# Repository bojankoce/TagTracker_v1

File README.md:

# TagTracker_v1
Version 1 of the Tag Tracker

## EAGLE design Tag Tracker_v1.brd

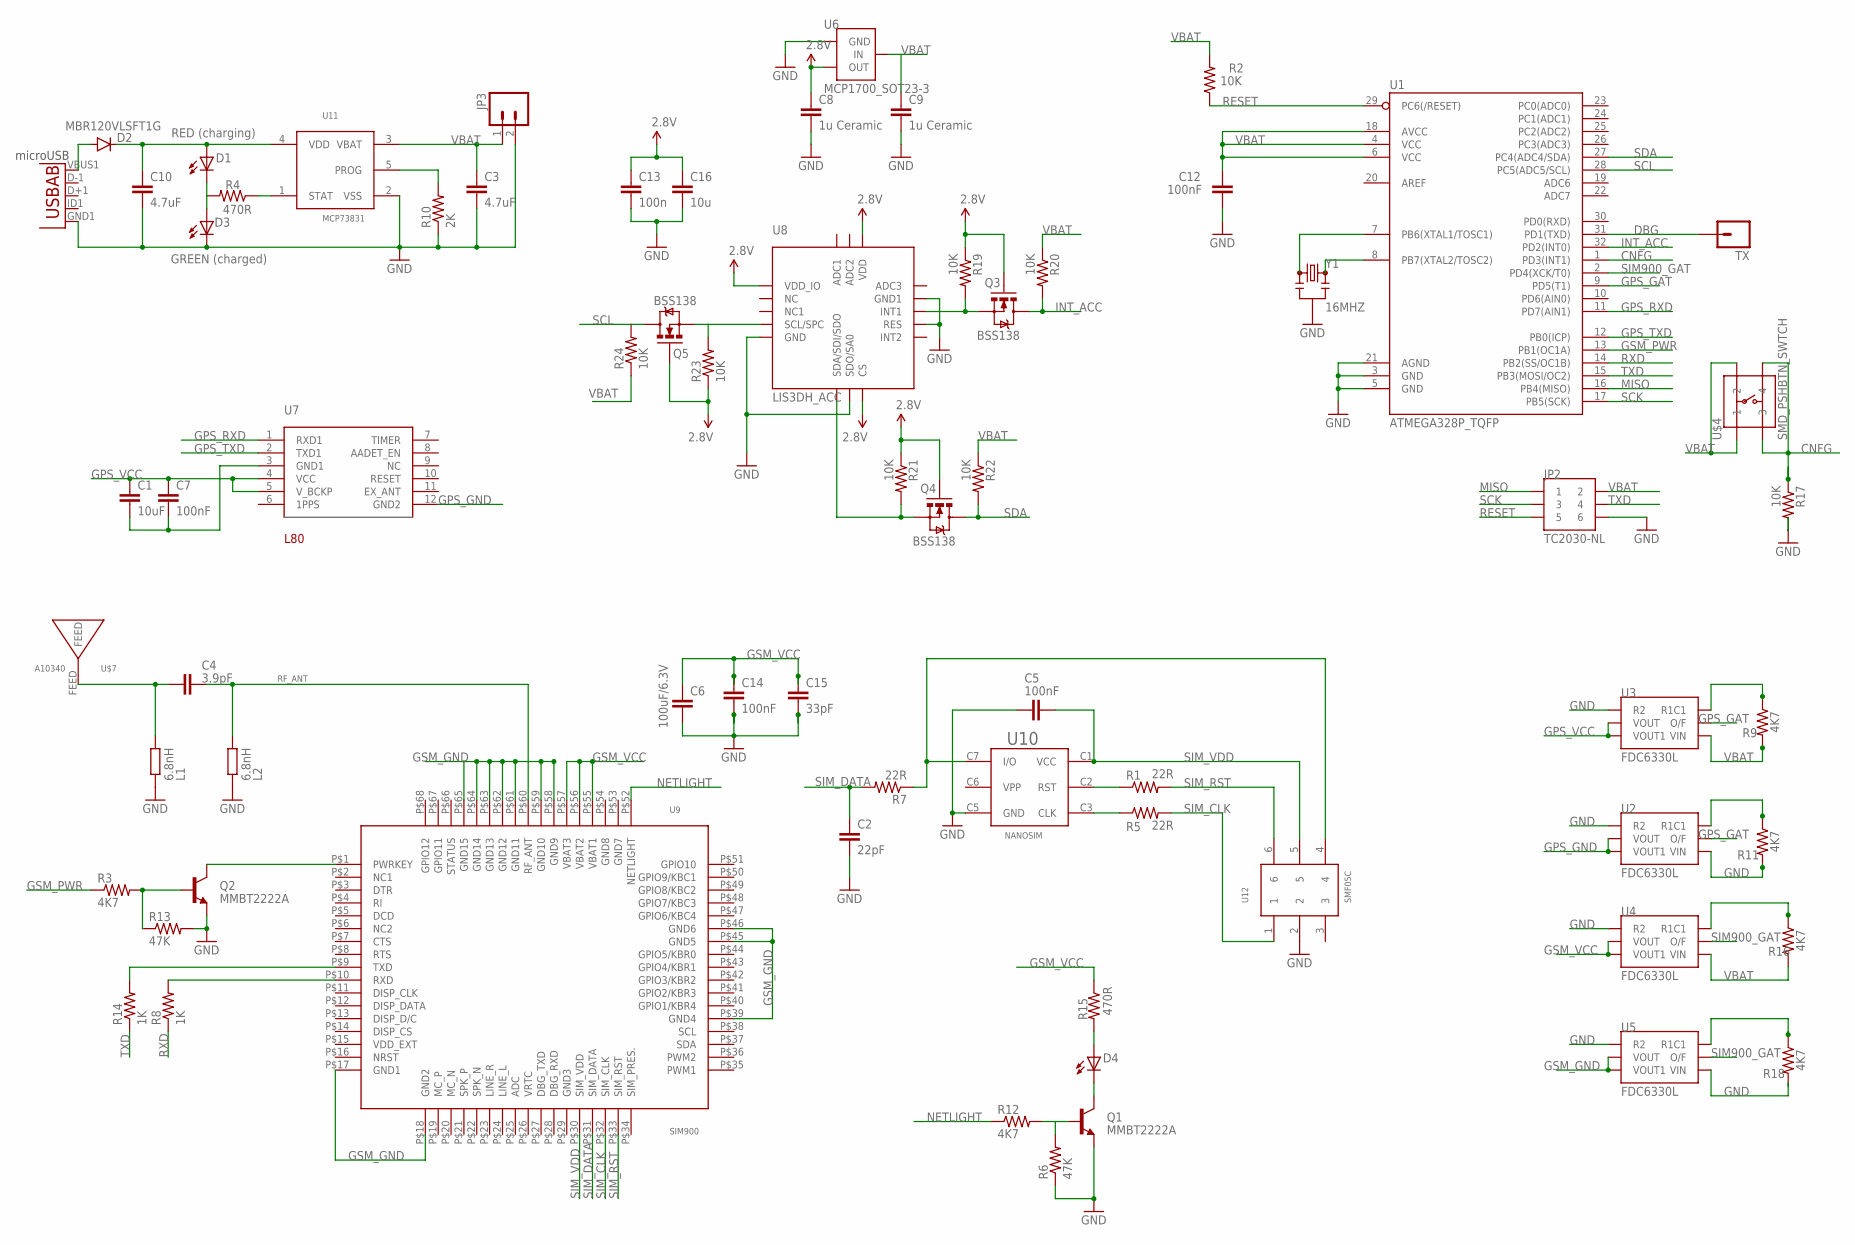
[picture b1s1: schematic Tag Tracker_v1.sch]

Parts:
C1: 10uF; 0603-CAP
C2: 22pF; 0603-CAP
C3, C10: 4.7uF; 0603-CAP
C4: 3.9pF; C0603-ROUND
C5, C7, C12, C14: 100nF; 0603-CAP
C6: 100uF/6.3V; 1206
C8, C9: 1u Ceramic; 0603-CAP
C13: 100n; 0603-CAP
C15: 33pF; 0603-CAP
C16: 10u; 0603-CAP
D1: RED (charging); SML0603
D2: MBR120VLSFT1G; SOD-123
D3: GREEN (charged); SML0603
D4: LEDSML0603; SML0603
JP2: TC2030-NL
JP3: M02PTH; 1X02
L1, L2: 6.8nH; R0603-ROUND
MICRO_USB: Micro USB; USB-AB-MICRO-SMD_V03
Q1, Q2: MMBT2222A; SOT23-3
Q3, Q4, Q5: BSS138; SOT23-3
R1, R5, R7: 22R; 0603-RES
R2, R17, R19, R20, R21, R22, R23, R24: 10K; 0603-RES
R3, R9, R11, R12, R16, R18: 4K7; 0603-RES
R4, R15: 470R; 0603-RES
R6, R13: 47K; 0603-RES
R8, R14: 1K; 0603-RES
R10: 2K; 0603-RES
TX: M01PTH; 1X01
U1: ATMEGA328P_TQFP; TQFP32-08
U2, U3, U4, U5: FDC6330L
U6: MCP1700_SOT23-3
U7: L80
U8: LIS3DH_ACC
U9: SIM900
U10: NANOSIM
U11: MCP73831; SOT23-5
U12: SMF05C; SC70-6
U$4: SMD_PSHBTN_SWTCH; KPT-1187B
U$7: A10340; CALVUS_5BAND_SMD_A10340_0MM_EXCLUSION
Y1: 16MHZ; RESONATOR-SMD

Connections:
2.8V: C8.1, C13.1, C16.1, Q3.1 (G), Q4.1 (G), Q5.1 (G), R19.1, R21.1, R23.1, U6.P$2 (OUT), U8.P$1 (VDD_IO), U8.P$8 (CS), U8.P$14 (VDD)
CNFG: R17.1, U1.1 (PD3(INT1)), U$4.P$3 (3), U$4.P$4 (4)
DBG: TX.1, U1.31 (PD1(TXD))
GND: C2.2, C3.2, C5.2, C6.2, C8.2, C9.2, C10.2, C12.2, C13.2, C14.2, C15.2, C16.2, D3.C, JP2.P$6 (6), JP3.2, L1.1, L2.1, MICRO_USB.GND1 (GND), Q1.2 (E), Q2.2 (E), R6.1, R10.1, R11.2, R13.2, R17.2, R18.2, U1.3 (GND), U1.5 (GND), U1.21 (AGND), U2.P$1 (R2), U2.P$4 (VIN), U3.P$1 (R2), U4.P$1 (R2), U5.P$1 (R2), U5.P$4 (VIN), U6.P$1 (GND), U8.P$5 (GND), U8.P$7 (SDO/SA0), U8.P$10 (RES), U8.P$12 (GND1), U10.C5 (GND), U11.2 (VSS), U12.2, Y1.2
GPS_GAT: U1.9 (PD5(T1)), U2.P$5 (O/F), U3.P$5 (O/F)
GPS_GND: C1.2, C7.2, U2.P$2 (VOUT), U2.P$3 (VOUT1), U7.3 (GND1), U7.12 (GND2)
GPS_RXD: U1.11 (PD7(AIN1)), U7.1 (RXD1)
GPS_TXD: U1.12 (PB0(ICP)), U7.2 (TXD1)
GPS_VCC: C1.1, C7.1, U3.P$2 (VOUT), U3.P$3 (VOUT1), U7.4 (VCC), U7.5 (V_BCKP)
GSM_GND: U5.P$2 (VOUT), U5.P$3 (VOUT1), U9.P$17 (GND1), U9.P$18 (GND2), U9.P$39 (GND4), U9.P$45 (GND5), U9.P$46 (GND6), U9.P$58 (GND9), U9.P$59 (GND10), U9.P$61 (GND11), U9.P$62 (GND12), U9.P$63 (GND13), U9.P$64 (GND14), U9.P$65 (GND15)
GSM_PWR: R3.1, U1.13 (PB1(OC1A))
GSM_VCC: C6.1, C14.1, C15.1, R15.1, U4.P$2 (VOUT), U4.P$3 (VOUT1), U9.P$55 (VBAT1), U9.P$56 (VBAT2), U9.P$57 (VBAT3)
INT_ACC: Q3.3 (D), R20.2, U1.32 (PD2(INT0))
MISO: JP2.P$1 (1), U1.16 (PB4(MISO))
unnamed: R7.1, U10.C7 (I/O), U12.4
unnamed: Q2.1 (B), R3.2, R13.1
unnamed: R1.1, U10.C2 (RST)
unnamed: U1.8 (PB7(XTAL2/TOSC2)), Y1.3
unnamed: R5.1, U10.C3 (CLK)
unnamed: U1.7 (PB6(XTAL1/TOSC1)), Y1.1
unnamed: R9.1, U3.P$6 (R1C1)
unnamed: R8.2, U9.P$10 (RXD)
unnamed: R14.2, U9.P$9 (TXD)
unnamed: Q2.3 (C), U9.P$1 (PWRKEY)
unnamed: R4.1, U11.1 (STAT)
unnamed: R11.1, U2.P$6 (R1C1)
unnamed: R10.2, U11.5 (PROG)
unnamed: D1.C, D3.A, R4.2
unnamed: D2.A, MICRO_USB.VBUS1 (VBUS)
unnamed: C4.2, L1.2, U$7.FEED
unnamed: C10.1, D1.A, D2.C, U11.4 (VDD)
unnamed: Q1.1 (B), R6.2, R12.2
unnamed: R16.1, U4.P$6 (R1C1)
unnamed: R18.1, U5.P$6 (R1C1)
unnamed: D4.C, Q1.3 (C)
unnamed: D4.A, R15.2
unnamed: Q3.2 (S), R19.2, U8.P$11 (INT1)
unnamed: Q4.2 (S), R21.2, U8.P$6 (SDA/SDI/SDO)
unnamed: Q5.2 (S), R23.2, U8.P$4 (SCL/SPC)
NETLIGHT: R12.1, U9.P$52 (NETLIGHT)
RESET: JP2.P$5 (5), R2.1, U1.29 (PC6(/RESET))
RF_ANT: C4.1, L2.2, U9.P$60 (RF_ANT)
RXD: R8.1, U1.14 (PB2(SS/OC1B))
SCK: JP2.P$3 (3), U1.17 (PB5(SCK))
SCL: Q5.3 (D), R24.2, U1.28 (PC5(ADC5/SCL))
SDA: Q4.3 (D), R22.2, U1.27 (PC4(ADC4/SDA))
SIM900_GAT: U1.2 (PD4(XCK/T0)), U4.P$5 (O/F), U5.P$5 (O/F)
SIM_CLK: R5.2, U9.P$32 (SIM_CLK), U12.1
SIM_DATA: C2.1, R7.2, U9.P$31 (SIM_DATA)
SIM_RST: R1.2, U9.P$33 (SIM_RST), U12.6
SIM_VDD: C5.1, U9.P$30 (SIM_VDD), U10.C1 (VCC), U12.5
TXD: JP2.P$4 (4), R14.1, U1.15 (PB3(MOSI/OC2))
VBAT: C3.1, C9.1, C12.1, JP2.P$2 (2), JP3.1, R2.2, R9.2, R16.2, R20.1, R22.1, R24.1, U1.4 (VCC), U1.6 (VCC), U1.18 (AVCC), U3.P$4 (VIN), U4.P$4 (VIN), U6.P$3 (IN), U11.3 (VBAT), U$4.P$1 (1), U$4.P$2 (2)

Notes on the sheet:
RF_ANT
microUSB

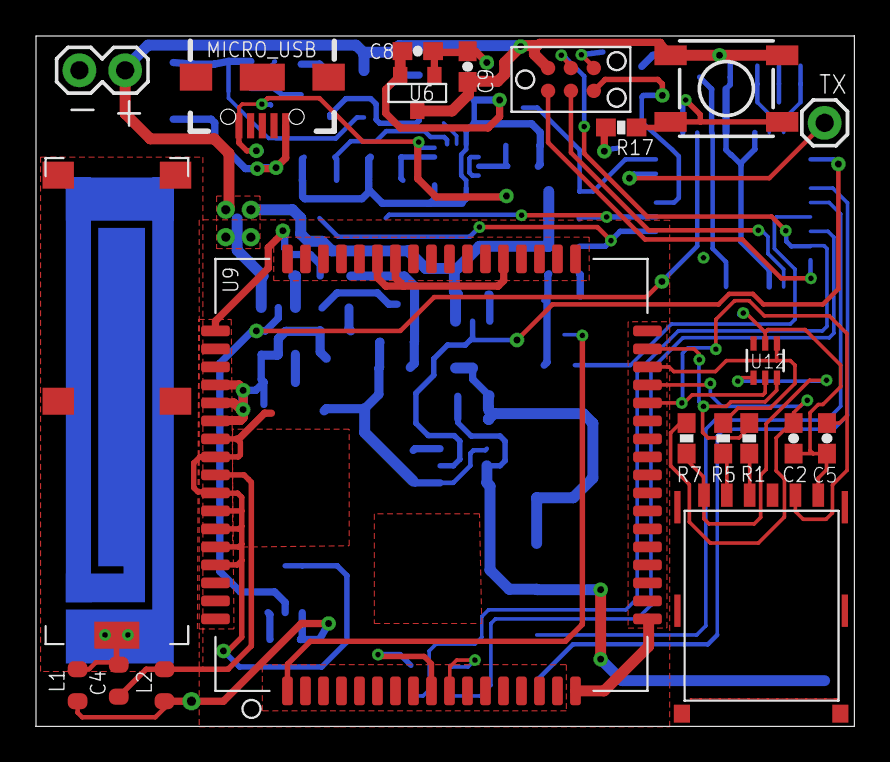
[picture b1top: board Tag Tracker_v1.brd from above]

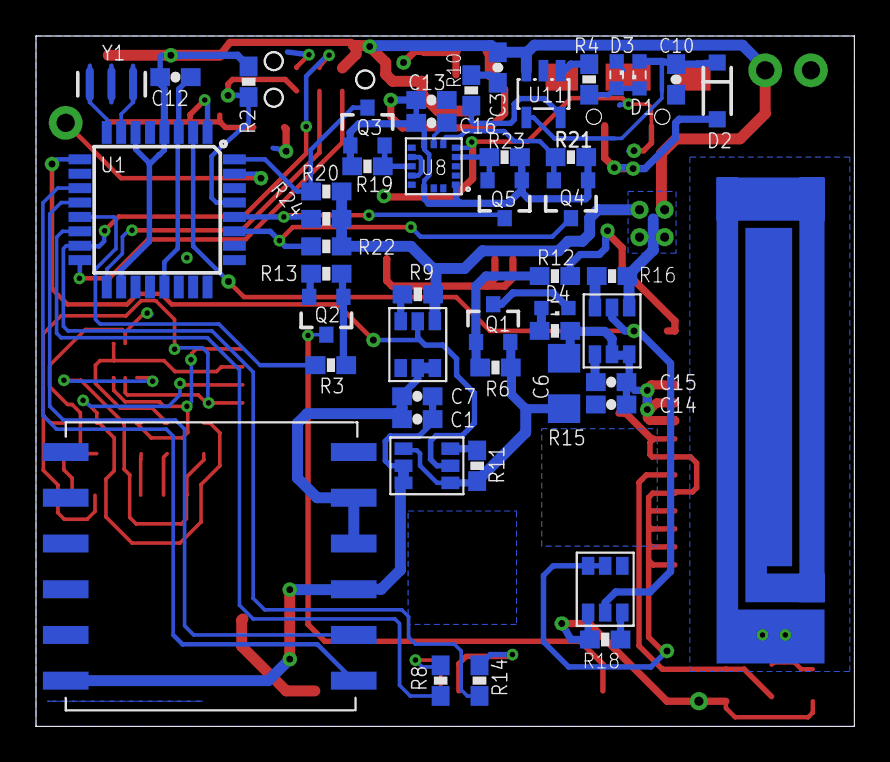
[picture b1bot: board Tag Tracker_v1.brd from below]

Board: 2 copper layers, 45.3 x 38.2 mm, 69 parts (48 on the bottom side), 53 nets.

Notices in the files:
parts and their libraries:
SparkFun-Capacitors: Licensing: CC v3.0 Share-Alike You are welcome to use this library for commercial purposes.
SparkFun-DiscreteSemi: Licensing: Creative Commons ShareAlike 4.0 International - https://creativecommons.org/licenses/by-sa/4.0
